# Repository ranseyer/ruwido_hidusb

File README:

************************************************
*                                              *
* RUWIDO V-USB-HID Receiver by Alexander Meyer *
*                                              *
************************************************

This Code is a blend of V-USB and the Ruwido decoder by Guenter Bartsch.
It runs on the ATMega8 as well as the 48-328 family. You also need a
56kHz IR-receiver, e.g. the TSOP1756.

See http://vusb.wikidot.com/hardware for general information on the
USB-interface.

This Package is configured for the USBASP,solder the TSOP output to PIND3 of the controller.

/* ---------------------------- Hardware Config ---------------------------- */

#define USB_CFG_IOPORTNAME      B
/* This is the port where the USB bus is connected. When you configure it to
 * "B", the registers PORTB, PINB and DDRB will be used.
 */
#define USB_CFG_DMINUS_BIT      0
/* This is the bit number in USB_CFG_IOPORT where the USB D- line is connected.
 * This may be any bit in the port.
 */
#define USB_CFG_DPLUS_BIT       1
/* This is the bit number in USB_CFG_IOPORT where the USB D+ line is connected.
 * This may be any bit in the port. Please note that D+ must also be connected
 * to interrupt pin INT0!
 */

This Package is configured for the USBASP,solder the TSOP output to PIND3 of the controller.

TODO:

Aggregation of modifyers does not work correctly yet.
Not all Keycodes are mapped since I didn't find codes for some of the Keys
in the USB-HID spec.

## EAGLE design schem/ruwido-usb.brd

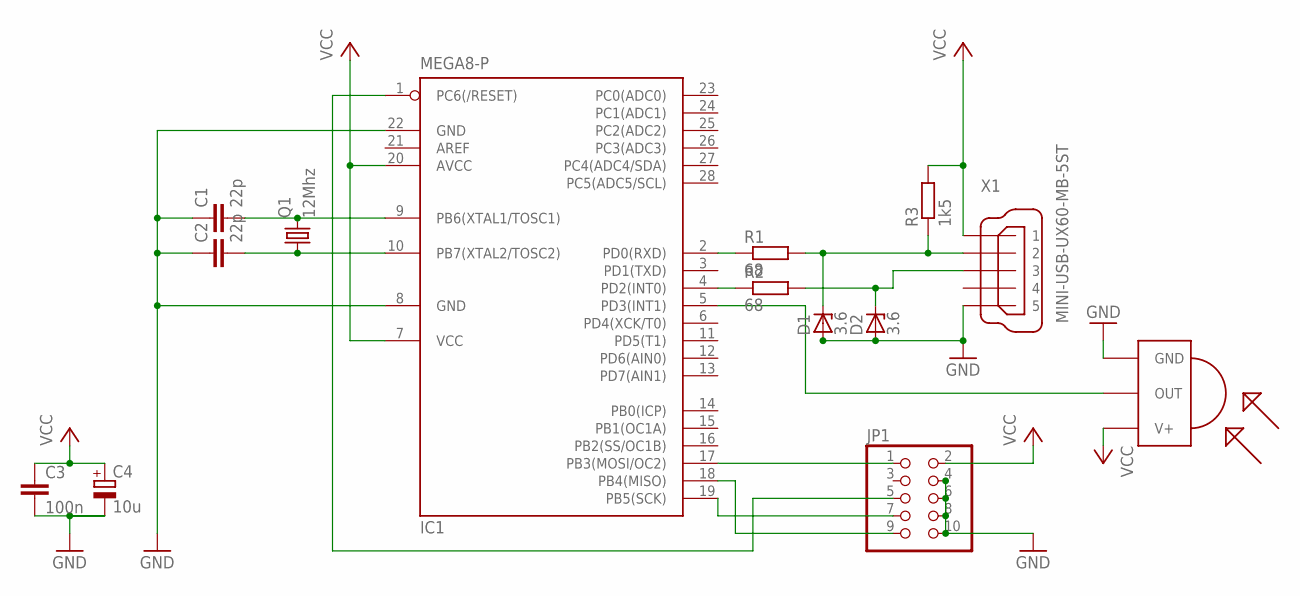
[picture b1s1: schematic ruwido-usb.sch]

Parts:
C1, C2: 22p; C025-024X044
C3: 100n; C025-024X044
C4: 10u; E2,5-6
D1, D2: 3.6; DO34Z7
IC1: MEGA8-P; DIL28-3
JP1: PINHD-2X5; 2X05
Q1: 12Mhz; HC49U70
R1, R2: 68; 0204/7
R3: 1k5; 0204/7
U$1: TSOP1756; TSOP17XX
X1: MINI-USB-UX60-MB-5ST; UX60-MB-5ST

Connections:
GND: C1.1, C2.1, C3.2, C4.-, D1.A, D2.A, IC1.8 (GND), IC1.22 (GND), JP1.4, JP1.6, JP1.8, JP1.10, U$1.GND, X1.5
unnamed: IC1.2 (PD0(RXD)), R1.1
unnamed: D1.C, R1.2, R3.1, X1.2
unnamed: IC1.4 (PD2(INT0)), R2.1
unnamed: D2.C, R2.2, X1.3
unnamed: C1.2, IC1.9 (PB6(XTAL1/TOSC1)), Q1.2
unnamed: C2.2, IC1.10 (PB7(XTAL2/TOSC2)), Q1.1
unnamed: IC1.5 (PD3(INT1)), U$1.OUT
unnamed: IC1.1 (PC6(/RESET)), JP1.5
unnamed: IC1.17 (PB3(MOSI/OC2)), JP1.1
unnamed: IC1.19 (PB5(SCK)), JP1.7
unnamed: IC1.18 (PB4(MISO)), JP1.9
VCC: C3.1, C4.+, IC1.7 (VCC), IC1.20 (AVCC), JP1.2, R3.2, U$1.V+, X1.1

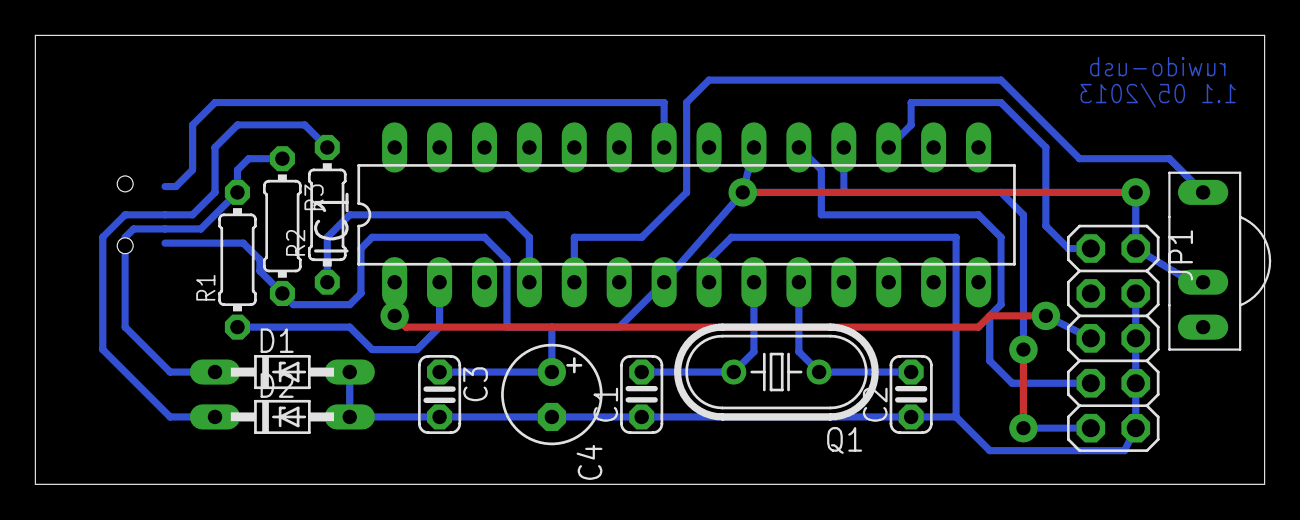
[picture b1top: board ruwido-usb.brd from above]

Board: 2 copper layers, 69.5 x 25.4 mm, 14 parts (1 on the bottom side), 13 nets.

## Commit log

2013-05-01 Use Arduino to program.
2013-05-01 Changes seemingly needed for newer avrgcc.
2013-05-09 Got a new USB programmer.
2013-05-09 Added EAGLE files.
2014-06-22 Some minor bugs fixed
2014-07-29 Configuration for USB ASP
